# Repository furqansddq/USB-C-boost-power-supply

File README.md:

# USB-C-boost-power-supply
A compact hardware module designed in KiCAD that steps up standard USB Type-C input to a configurable 5V–28V DC output using an MT3608 boost converter topology. Features integrated MAX17048 real-time battery fuel gauge monitoring, simulated transient filtering, low voltage ripple, and dedicated USB-C CC termination.

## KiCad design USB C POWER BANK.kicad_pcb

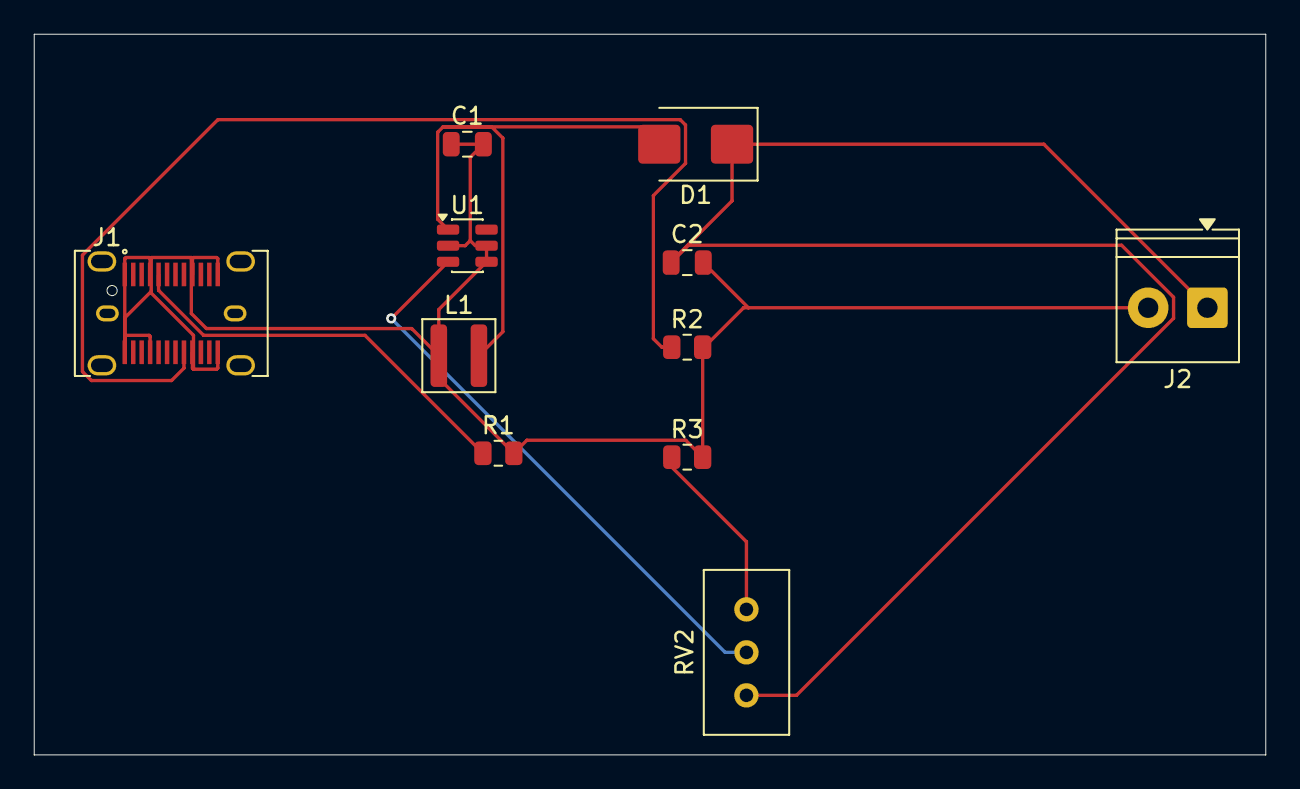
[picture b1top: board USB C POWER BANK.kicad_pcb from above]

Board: 2 copper layers, 72.8 x 42.6 mm, 11 parts (0 on the bottom side), 7 nets.

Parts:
C1: 10uF; C_0805_2012Metric
C2: 22uF; C_0805_2012Metric
D1: SS34; D_SMB
J1: USB_C_Receptacle; USB_C_Receptacle_JAE_DX07S024WJ1R350
J2: Screw_Terminal_01x02; TerminalBlock_Phoenix_PT-1,5-2-3.5-H_1x02_P3.50mm_Horizontal
L1: L; L_Wuerth_MAPI-4020
R1, R2: 5.1K; R_0805_2012Metric
R3: 2K; R_0805_2012Metric
RV2: R_Potentiometer; Potentiometer_Bourns_3296W_Vertical
U1: MT3608; SOT-23-6

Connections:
unnamed: D1.2 (A), L1.2, U1.1 (SW)
unnamed: C2.1, D1.1 (K), J2.1, RV2.3
unnamed: J1.A5 (CC1), R1.1
unnamed: J1.B5 (CC2), R2.1
unnamed: C1.1, C1.2, C2.2, J1.A1 (GND), J1.A4 (VBUS), J1.A9 (VBUS), J1.A12 (GND), J1.B1 (GND), J1.B4 (VBUS), J1.B9 (VBUS), J1.B12 (GND), J2.2, L1.1, R1.2, R2.2, R3.2, U1.2 (GND), U1.4 (EN), U1.5 (IN)
unnamed: R3.1, RV2.1
unnamed: RV2.2, U1.3 (FB)
